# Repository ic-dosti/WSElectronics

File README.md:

# About authors:
- Esmagambet Doshan
- Tumanov Artyom

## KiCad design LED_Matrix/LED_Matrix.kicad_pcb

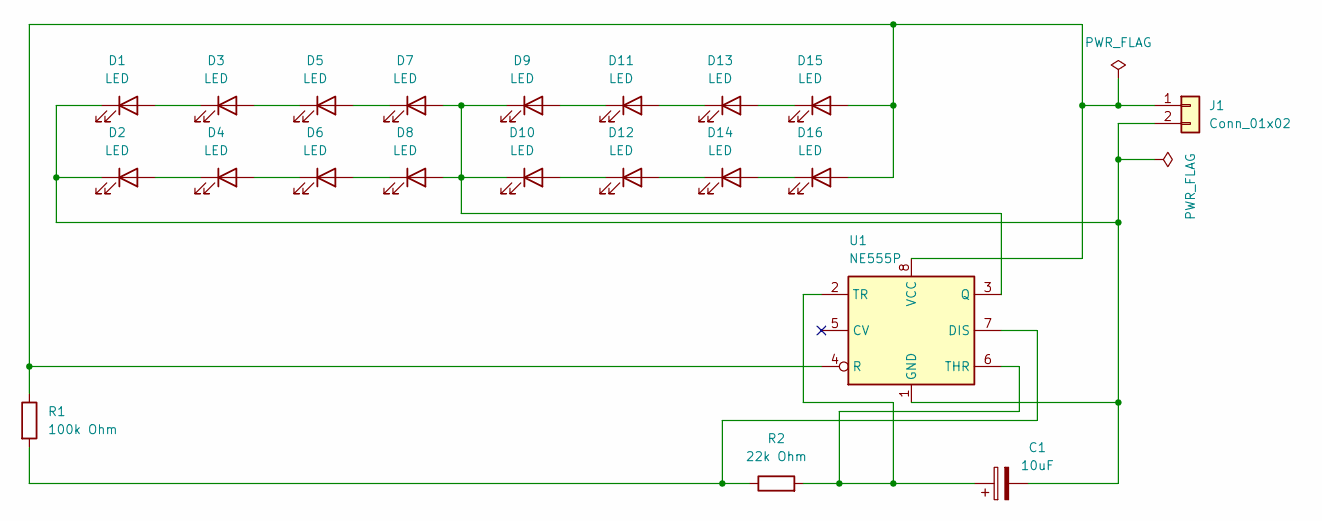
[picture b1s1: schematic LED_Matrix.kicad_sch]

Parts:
C1: 10uF; CP_Radial_D4.0mm_P2.00mm
D1, D2, D3, D4, D5, D6, D7, D8, D9, D10, D11, D12, D13, D14, D15, D16: LED; LED_0805_2012Metric
J1: Conn_01x02; PinHeader_1x02_P2.54mm_Horizontal
R1: 100k Ohm; R_Axial_DIN0309_L9.0mm_D3.2mm_P12.70mm_Horizontal
R2: 22k Ohm; R_Axial_DIN0309_L9.0mm_D3.2mm_P12.70mm_Horizontal
U1: NE555P; DIP-8_W7.62mm

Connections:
unnamed: C1.1, R2.2, U1.2 (TR), U1.6 (THR)
unnamed: C1.2, D1.1 (K), D2.1 (K), J1.2, U1.1 (GND)
unnamed: D1.2 (A), D3.1 (K)
unnamed: D2.2 (A), D4.1 (K)
unnamed: D3.2 (A), D5.1 (K)
unnamed: D4.2 (A), D6.1 (K)
unnamed: D5.2 (A), D7.1 (K)
unnamed: D6.2 (A), D8.1 (K)
unnamed: D7.2 (A), D8.2 (A), D9.1 (K), D10.1 (K), U1.3 (Q)
unnamed: D10.2 (A), D12.1 (K)
unnamed: D9.2 (A), D11.1 (K)
unnamed: D11.2 (A), D13.1 (K)
unnamed: D12.2 (A), D14.1 (K)
unnamed: D13.2 (A), D15.1 (K)
unnamed: D14.2 (A), D16.1 (K)
unnamed: D15.2 (A), D16.2 (A), J1.1, R1.1, U1.4 (R), U1.8 (VCC)
unnamed: R1.2, R2.1, U1.7 (DIS)

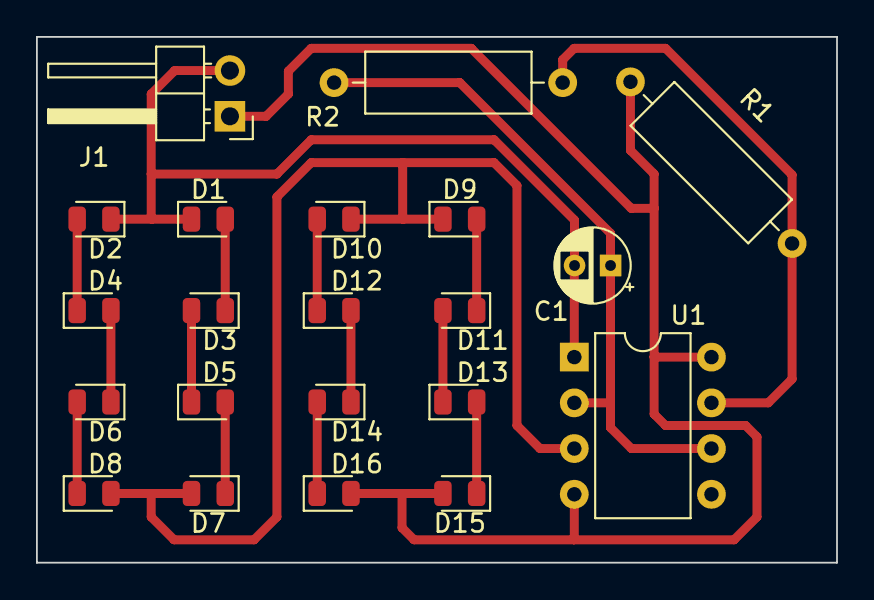
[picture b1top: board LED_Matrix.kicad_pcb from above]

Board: 2 copper layers, 44.5 x 29.2 mm, 21 parts (0 on the bottom side), 17 nets.

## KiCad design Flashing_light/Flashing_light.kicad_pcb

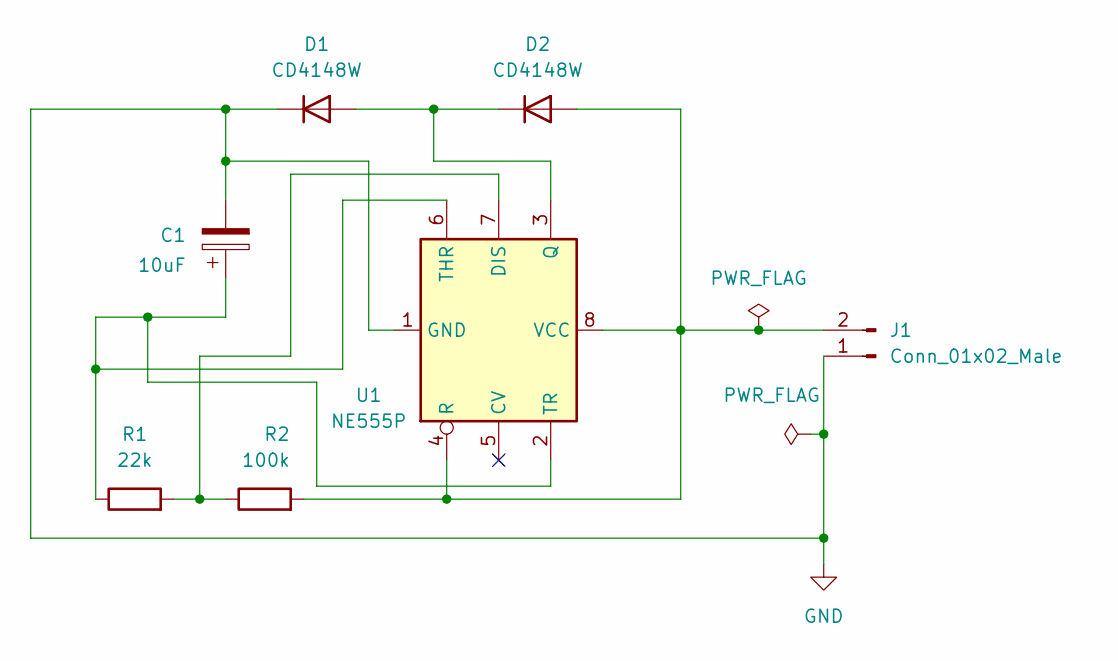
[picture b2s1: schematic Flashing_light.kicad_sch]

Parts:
C1: 10uF; CP_Radial_D4.0mm_P2.00mm
D1, D2: CD4148W; D_0805_2012Metric
J1: Conn_01x02_Male; PinHeader_1x02_P2.54mm_Horizontal
R1: 22k; R_Axial_DIN0309_L9.0mm_D3.2mm_P12.70mm_Horizontal
R2: 100k; R_Axial_DIN0309_L9.0mm_D3.2mm_P12.70mm_Horizontal
U1: NE555P; DIP-8_W7.62mm

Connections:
GND: C1.2, D1.1 (K), J1.1, U1.1 (GND)
unnamed: C1.1, R1.1, U1.2 (TR), U1.6 (THR)
unnamed: D1.2 (A), D2.1 (K), U1.3 (Q)
unnamed: D2.2 (A), J1.2, R2.2, U1.4 (R), U1.8 (VCC)
unnamed: R1.2, R2.1, U1.7 (DIS)

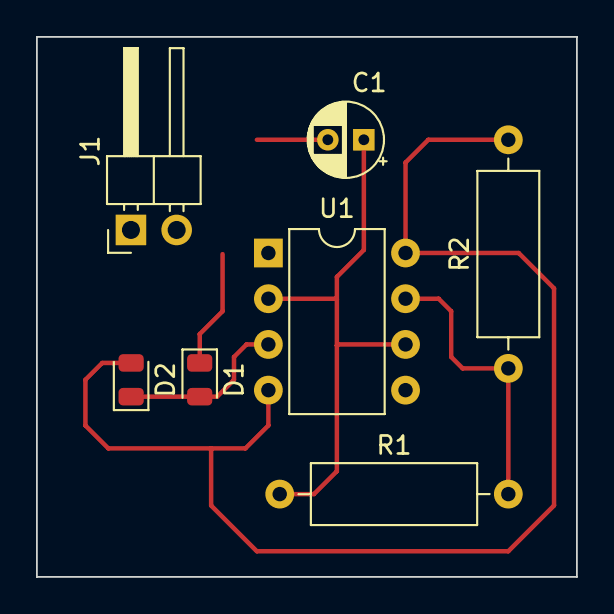
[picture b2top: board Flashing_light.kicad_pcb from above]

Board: 2 copper layers, 30.0 x 30.0 mm, 7 parts (0 on the bottom side), 5 nets.

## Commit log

2022-12-03 20220312_1102
2022-12-03 20220312_110250
2022-12-03 20221203_110311
2022-12-03 20221203_110404
2022-12-09 20221209_081340
2022-12-09 20221209_081450
2022-12-10 first project commit
2022-12-10 add OpAmpDevBoard folders
2022-12-16 add smile scheme
2023-02-14 20230214_084256
2023-03-16 Second
2023-03-18 Add Music_box, Sound_amplifier, FM_Radio
2023-03-18 Changes in README
2023-03-18 Some Changes in README
2023-03-18 20230318_174200
2023-03-27 20230327_130600
2023-05-07 new structure
2023-06-30 20230630_1928
2023-08-04 20230804_0943
2023-08-12 20230812_1329
2023-09-21 20230921_1612
2023-11-09 20231109_1634
2024-01-22 20240122_0919
2024-01-22 20240122_091902
2024-01-22 20240122_0931
2024-01-26 20240126_1629
2024-01-27 20240127_0832
2024-02-09 20240209_1101
2024-03-12 20240312_1123
2024-03-16 20240316_1637
2024-03-20 20240320_1330
2024-03-22 20240322_2133
2024-03-22 20240322_2136
2024-04-12 20240412_1645
2024-08-05 20240805_1823
